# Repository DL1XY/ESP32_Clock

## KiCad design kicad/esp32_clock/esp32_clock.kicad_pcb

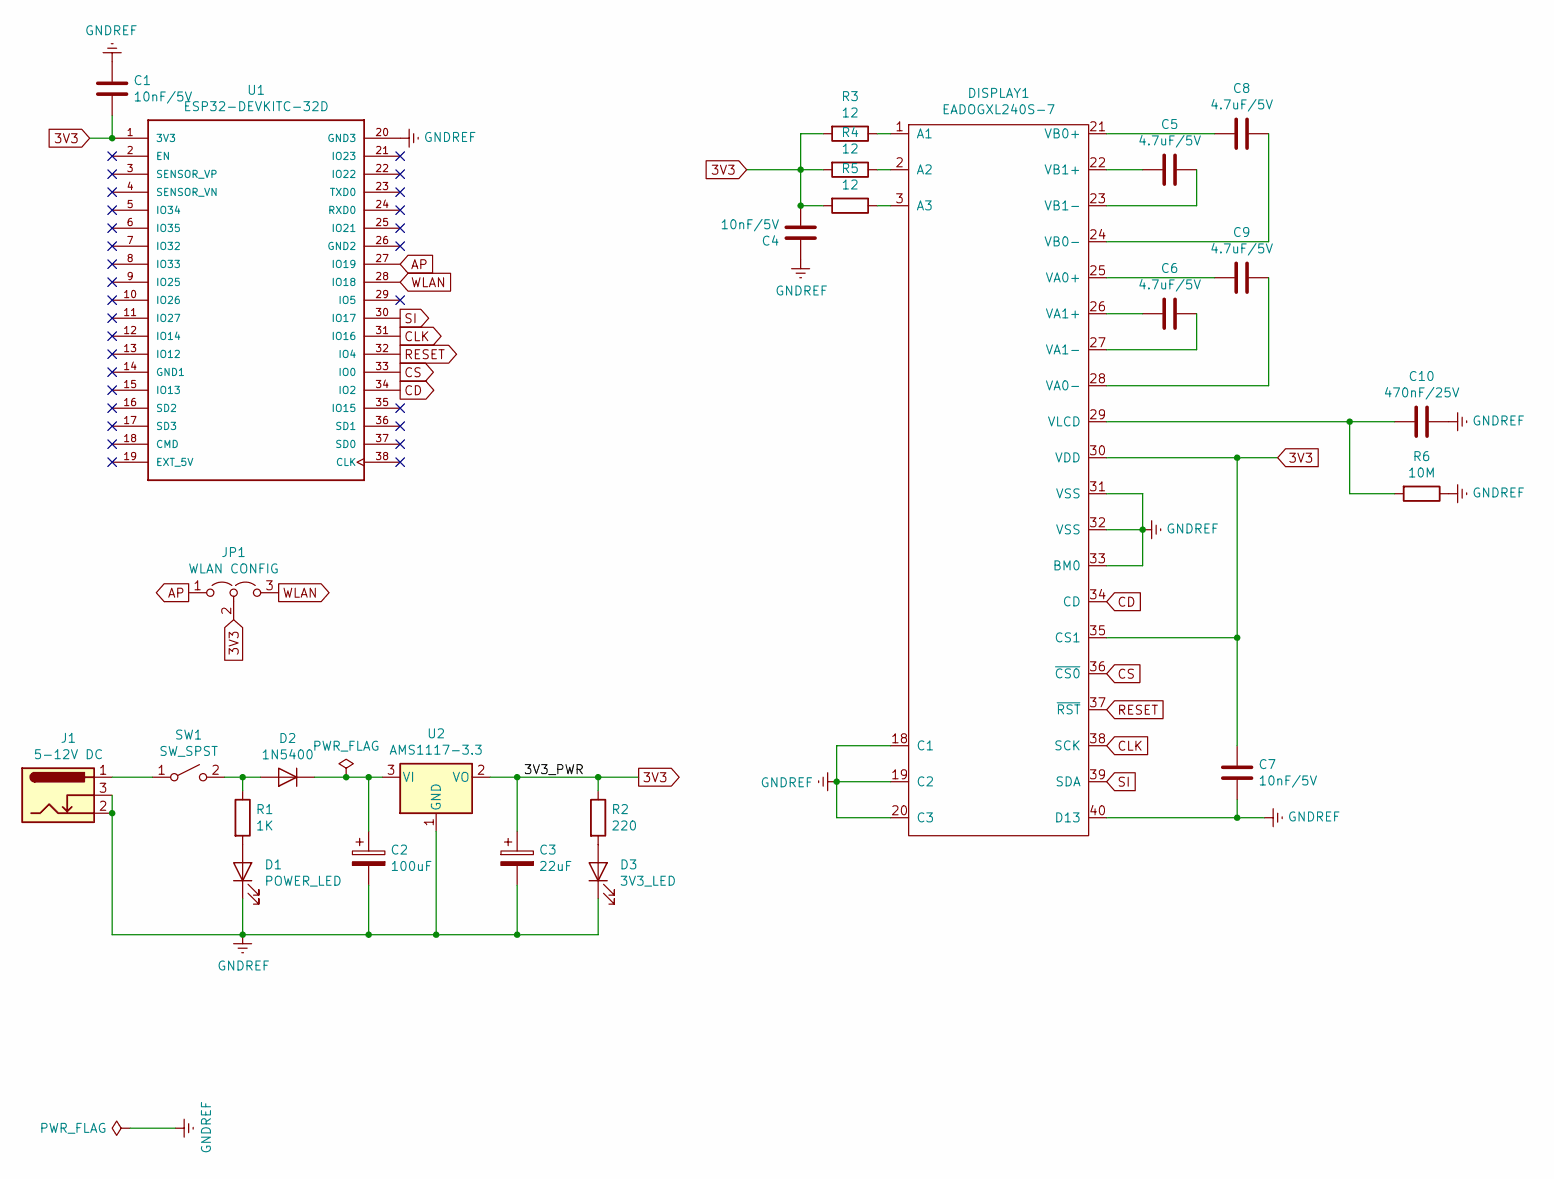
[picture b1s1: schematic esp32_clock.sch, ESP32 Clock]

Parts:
C1, C4, C7: 10nF/5V; C_Disc_D4.3mm_W1.9mm_P5.00mm
C2: 100uF; CP_Radial_D6.3mm_P2.50mm
C3: 22uF; CP_Radial_D5.0mm_P2.00mm
C5, C6, C8, C9: 4.7uF/5V; C_Disc_D4.3mm_W1.9mm_P5.00mm
C10: 470nF/25V; C_Disc_D4.3mm_W1.9mm_P5.00mm
D1: POWER_LED; LED_D5.0mm
D2: 1N5400; D_DO-34_SOD68_P10.16mm_Horizontal
D3: 3V3_LED; LED_D5.0mm
DISPLAY1: EADOGXL240S-7; EA DOGXL240-7
J1: 5-12V DC; BarrelJack_Horizontal
JP1: WLAN CONFIG; PinHeader_1x03_P2.54mm_Vertical
R1: 1K; R_Axial_DIN0204_L3.6mm_D1.6mm_P7.62mm_Horizontal
R2: 220; R_Axial_DIN0204_L3.6mm_D1.6mm_P7.62mm_Horizontal
R3, R4, R5: 12; R_Axial_DIN0204_L3.6mm_D1.6mm_P7.62mm_Horizontal
R6: 10M; R_Axial_DIN0204_L3.6mm_D1.6mm_P7.62mm_Horizontal
SW1: SW_SPST; SW_DIP_SPSTx01_Slide_6.7x4.1mm_W7.62mm_P2.54mm_LowProfile
U1: ESP32-DEVKITC-32D; ESP32-WROOM-Devkit
U2: AMS1117-3.3; TO-220-3_Vertical

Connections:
3V3: C1.2, C3.1, C4.2, C7.1, DISPLAY1.30 (VDD), DISPLAY1.35 (CS1), JP1.2 (C), R2.1, R3.2, R4.2, R5.2, U1.1 (3V3), U2.2 (VO)
AP: JP1.1 (A), U1.27 (IO19)
CD: DISPLAY1.34 (CD), U1.34 (IO2)
CLK: DISPLAY1.38 (SCK), U1.31 (IO16)
CS: DISPLAY1.36 (~CS0), U1.33 (IO0)
GNDREF: C1.1, C2.2, C3.2, C4.1, C7.2, C10.1, D1.1 (K), D3.1 (K), DISPLAY1.18 (C1), DISPLAY1.19 (C2), DISPLAY1.20 (C3), DISPLAY1.31 (VSS), DISPLAY1.32 (VSS), DISPLAY1.33 (BM0), DISPLAY1.40 (D13), J1.2, J1.3, R6.1, U1.20 (GND3), U2.1 (GND)
unnamed: C2.1, D2.1 (K), U2.3 (VI)
unnamed: C5.1, DISPLAY1.23 (VB1-)
unnamed: C5.2, DISPLAY1.22 (VB1+)
unnamed: C6.1, DISPLAY1.27 (VA1-)
unnamed: C6.2, DISPLAY1.26 (VA1+)
unnamed: C8.1, DISPLAY1.24 (VB0-)
unnamed: C8.2, DISPLAY1.21 (VB0+)
unnamed: C9.1, DISPLAY1.28 (VA0-)
unnamed: C9.2, DISPLAY1.25 (VA0+)
unnamed: C10.2, DISPLAY1.29 (VLCD), R6.2
unnamed: D1.2 (A), R1.2
unnamed: D2.2 (A), R1.1, SW1.2 (B)
unnamed: D3.2 (A), R2.2
unnamed: DISPLAY1.1 (A1), R3.1
unnamed: DISPLAY1.2 (A2), R4.1
unnamed: DISPLAY1.3 (A3), R5.1
unnamed: J1.1, SW1.1 (A)
RESET: DISPLAY1.37 (~RST), U1.32 (IO4)
SI: DISPLAY1.39 (SDA), U1.30 (IO17)
WLAN: JP1.3 (B), U1.28 (IO18)

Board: 2 copper layers, 25 parts (0 on the bottom side), 26 nets, no tracks yet.

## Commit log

2020-05-02 init
